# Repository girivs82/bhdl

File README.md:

# BHDL - Board Hardware Description Language

**A modern hardware description language for electronic circuit design with natural flow-based syntax, intelligent analysis, and professional tooling.**

---

## 🎯 Overview

BHDL enables hardware designers to express circuit designs the way they think about them - as **flows of power and signals** between components. With automatic component inference, electrical validation, and comprehensive IDE integration, BHDL brings software-grade tooling to hardware design.

```bhdl
board PowerSupply {
    power VIN = 12V @ 2A;
    ground GND;

    // Flow-based syntax: intuitive and readable
    net regulated: VIN -> reg: LM7805().IN;
    reg.OUT -> @VCC;
    reg.GND -> @GND;

    // Design intent capture
    net filtered: @VCC -> cap: Cap(10µF).1 -> cap.2 -> @GND
        for noise_filtering(cutoff: 100Hz, attenuation: 40dB);
}
```

## ✨ Key Features

### 🌊 Natural Flow-Based Syntax
- **Express circuits as flows**: `VCC -> Res(1kΩ).1 -> LED(red).A -> GND`
- **Component instantiation in-line**: No separate declaration/instantiation
- **Multiple connection operators**: `->` (unidirectional), `<->` (bidirectional), `|>` (flow)
- **Net assignments**: `protected_vin: TVSDiode(15V).K` creates nets with implicit handles

### 🎨 Design Intent System
- **Capture design purpose**: 38 standard intent functions
- **Flow-based annotation**: `for current_limiting(max_current: 20mA)`
- **Automatic synthesis hints**: Tools understand design intent
- **Simulation mode determination**: PureDigital, DigitalWithTiming, MixedSignal, AnalogRequired
- **Validation rules**: Intent-specific checks and recommendations

### 🔬 Advanced Electrical Analysis
- **DC Operating Point**: Newton-Raphson nonlinear solver with component models
- **Safety Analysis**: Automatic derating, current limiting, protection recommendations
- **Component Role Detection**: Topology-based identification without naming conventions
- **Thermal Analysis**: Component temperature and hotspot detection
- **Power Domain Tracking**: Voltage propagation through complex hierarchies

### 📐 Power Domain Scalability
- **Wildcard expansion**: `sensor[*].VCC` → expands to all sensor instances
- **Range expansion**: `fpga.VCCO[0..7]` → 8 indexed pins
- **Automatic decoupling**: Capacitor generation with placement constraints
- **10-100x verbosity reduction** for large designs

### 💻 Professional Tooling

#### Command-Line Interface (CLI)
9 comprehensive commands for the complete workflow:
- `parse` - Syntax validation and AST inspection
- `analyze` - Full 11-pass semantic analysis
- `synthesize` - Netlist generation (JSON/SPICE formats)
- `visualize` - SVG schematic generation
- `spice` - Component role detection and analysis
- `pipeline` - End-to-end workflow automation
- `simulate` - Testbench-driven simulation
- `intents` - Flow tracking and intent analysis
- `doc` - Automatic documentation generation

```bash
# Complete workflow in one command
$ bhdl-cli circuit.bhdl pipeline -o ./build

# Analyze design intents
$ bhdl-cli circuit.bhdl intents

# Generate power domain docs
$ bhdl-cli circuit.bhdl doc -o power_analysis.md
```

#### Language Server Protocol (LSP)
22 major features for IDE integration:
- Real-time diagnostics (parse + semantic)
- Intelligent autocomplete (38 intent functions)
- Hover documentation
- Go to definition / Find references
- Symbol rename with conflict detection
- Document outline and workspace symbols
- Semantic syntax highlighting
- Code actions (quick fixes)
- Inlay hints (type/value display)
- Document formatting
- And 12 more features...

**Works with**: VSCode, Neovim, Emacs, Sublime Text, IntelliJ, and any LSP-compatible editor.

## 🚀 Quick Start

### Prerequisites
- Rust 1.70 or later
- 100MB disk space

### Installation

```bash
# Clone the repository
git clone https://github.com/[USERNAME]/bhdl.git
cd bhdl

# Build all components
cargo build --release

# Run tests
cargo test

# Build CLI
cargo build --release -p bhdl-cli

# Build LSP server
cargo build --release -p bhdl-lsp
```

### Your First Circuit

Create `led_blinker.bhdl`:

```bhdl
entity LED(color: string) {
    pin A: signal in;
    pin K: signal in;
}

entity Resistor(value: resistance) {
    pin 1: signal inout;
    pin 2: signal inout;
}

board LEDBlinker {
    power VCC = 5V @ 100mA;
    ground GND;

    // Current-limited LED with design intent
    net power_to_res: @VCC -> r1: Resistor(330).1;
    net res_to_led: r1.2 -> led1: LED("red").A
        for current_limiting(max_current: 20mA);
    net led_to_gnd: led1.K -> @GND;
}
```

Validate and analyze:

```bash
# Parse the circuit
$ bhdl-cli led_blinker.bhdl parse
✓ Parse successful

# Run analysis
$ bhdl-cli led_blinker.bhdl analyze
✓ Analysis successful - no issues found

# Generate visualization
$ bhdl-cli led_blinker.bhdl visualize -o led_blinker.svg
✓ Visualization generated
```

## 📚 Documentation

| Document | Description |
|----------|-------------|
| [Language Specification](docs/spec/BHDL_Complete_Specification.md) | Complete v2.0 language reference |
| [CLI Guide](docs/implementation/CLI_IMPLEMENTATION_GUIDE.md) | Command-line interface reference |
| [LSP Guide](docs/implementation/LSP_IMPLEMENTATION_SUMMARY.md) | IDE integration guide |
| [Developer Guide](CLAUDE.md) | Architecture and development instructions |
| [Examples](docs/examples/) | Sample circuits and tutorials |
| [Testing Guide](tests/TESTING.md) | Test organization and execution |

## 🏗️ Architecture

The BHDL toolchain follows a multi-stage pipeline:

```
┌──────────────┐    ┌─────────┐    ┌───────────┐    ┌──────────────┐    ┌─────────────┐
│ BHDL Source  │───▶│ Parser  │───▶│ Analyzer  │───▶│ Synthesizer  │───▶│ Visualizer  │
│  (.bhdl)     │    │ (CST)   │    │ (11-pass) │    │  (Netlist)   │    │    (SVG)    │
└──────────────┘    └─────────┘    └───────────┘    └──────────────┘    └─────────────┘
                                           │
                                           ▼
                                    ┌─────────────┐
                                    │ SPICE       │
                                    │ Analysis    │
                                    └─────────────┘
```

### Core Components

#### 1. **bhdl-parser** - Syntax Analysis
- Full v2.0 flow-based syntax support
- Rowan-based incremental parsing
- Comprehensive error recovery
- Electrical unit handling (kΩ, μF, MHz, etc.)

#### 2. **bhdl-analyzer** - Semantic Analysis
11-pass analysis pipeline:
1. **Scope Building**: Symbol tables and definition scopes
2. **Component Registry**: Early instance registration for scalability
3. **Power Domain Expansion**: Wildcards, ranges, and decoupling generation
4. **Reference Resolution**: Type checking and symbol binding
5. **Constant Evaluation**: Compile-time computation
6. **Bounds Checking**: Range validation
7. **Power Analysis**: Voltage propagation and domain tracking
8. **Component Inference**: Automatic component selection
9. **SPICE Synthesis**: Circuit model generation
10. **Attribute Analysis**: Custom attribute handling
11. **Flow Tracking**: Intent resolution and simulation mode determination

#### 3. **bhdl-synthesizer** - Netlist Generation
- Structural netlist output
- Component database integration
- Reference designator auto-generation (R1, D1, C1, etc.)
- Multiple output formats (JSON, SPICE)

#### 4. **bhdl-visualizer** - Schematic Generation
- Semantic layout algorithms
- Force-directed and analytical placement
- Intelligent routing with pathfinding
- Component symbol libraries
- SVG output with embedded metadata

#### 5. **bhdl-spice** - Electrical Analysis
- Newton-Raphson DC solver
- Nonlinear component models
- LED forward voltage modeling
- Diode Shockley equations
- Safety analysis with derating factors

#### 6. **bhdl-stdlib** - Component Library
- Standard component definitions
- Manufacturer datasheet parameters
- Intent function implementations (38 standard intents)
- Behavioral models

#### 7. **bhdl-testbench** - Simulation
- Testbench compiler
- Waveform generation (VCD, CSV, JSON)
- Assertion checking
- Measurement extraction

#### 8. **bhdl-cli** - Command-Line Interface
Production-ready CLI with 9 commands for complete workflow automation.

#### 9. **bhdl-lsp** - Language Server
Production-ready LSP server with 22 features for professional IDE integration.

## 🎓 Language Features

### Flow-Based Connections
```bhdl
// Direct flow syntax
VCC -> Res(1kΩ).1 -> LED(red).A -> GND

// Named nets
net signal_line: sensor.OUT -> filter.IN;

// Bidirectional
data_bus: controller <-> memory;

// With component instantiation
VCC -> r1: Resistor(330).1 -> r1.2 -> led: LED("red").A;
```

### Design Intents
```bhdl
// Capture design purpose
net debounced: button -> rc_filter
    for debounce(time: 50ms);

// Protection intent
net protected: input -> tvs: TVSDiode(6V).K
    for input_protection(max_voltage: 6V);

// Measurement intent
net monitored: @VCC -> sense_resistor -> load
    for current_sensing(max_current: 1A, accuracy: 1%);
```

### Power Domain Scalability
```bhdl
board SensorArray {
    power VCC = 3.3V @ 500mA;

    // Wildcard expansion - connects ALL sensor instances
    power_domain @VCC = 3.3V @ 500mA {
        distribution {
            sensor[*].VCC;  // Expands to sensor_0.VCC, sensor_1.VCC, ...
        }

        decoupling {
            // One capacitor near each sensor
            near sensor[*]: 100nF @ 1;
        }
    }

    // Range expansion - 8 indexed pins
    power_domain @VCCO = 2.5V @ 1A {
        distribution {
            fpga.VCCO[0..7];  // Expands to VCCO0..VCCO7
        }
    }
}
```

### Entity Definitions
```bhdl
entity VoltageRegulator(
    input_voltage: voltage,
    output_voltage: voltage,
    max_current: current
) {
    pin VIN: power in;
    pin VOUT: power out;
    pin GND: ground;
    pin EN: signal in when has_enable_pin;

    // Behavioral specification (optional)
    behavior {
        VOUT = output_voltage;
        efficiency = 0.85;
    }
}
```

### Conditional Logic
```bhdl
// Ternary operator
net regulated: vin -> (use_ldo ? ldo.IN : switcher.IN);

// Conditional pins
pin EN: signal in when has_enable_control;

// Conditional connections
if debug_mode {
    test_points: signals[*] -> TestPoint();
}
```

## 🔧 Development

### Building from Source

```bash
# Debug build (faster compilation)
cargo build

# Release build (optimized)
cargo build --release

# Build specific component
cargo build -p bhdl-analyzer
```

### Running Tests

```bash
# All tests
cargo test

# Specific crate
cargo test -p bhdl-analyzer

# With output
cargo test -- --nocapture

# Single test
cargo test test_name
```

### Code Quality

```bash
# Linting
cargo clippy

# Formatting
cargo fmt

# Check without building
cargo check
```

## 📊 Project Status

| Component | Status | Features | Tests | LOC |
|-----------|--------|----------|-------|-----|
| **Parser** | ✅ Production | Full v2.0 syntax | 150+ | 8,500 |
| **Analyzer** | ✅ Production | 11-pass analysis | 200+ | 15,000 |
| **Synthesizer** | ✅ Production | Multi-format output | 80+ | 5,000 |
| **Visualizer** | ✅ Production | Multiple layouts | 50+ | 6,000 |
| **SPICE** | ✅ Production | DC + safety | 100+ | 8,000 |
| **Stdlib** | ✅ Production | 38 intents | N/A | 3,000 |
| **Testbench** | ✅ Production | Full simulation | 40+ | 4,000 |
| **CLI** | ✅ Production | 9 commands | Validated | 1,050 |
| **LSP** | ✅ Production | 22 features | 92 | 6,117 |
| **Total** | - | - | **700+** | **56,667** |

### Recent Milestones (October 2025)

- ✅ **CLI Implementation**: Complete command-line interface with 9 commands
- ✅ **LSP Server**: Full IDE integration with 22 LSP features
- ✅ **Intent System**: Flow tracking and 38 standard intent functions
- ✅ **Power Domain Expansion**: Wildcards and ranges for scalability
- ✅ **Documentation Generation**: Automatic power domain docs
- ✅ **Unified Simulation**: DC + safety + thermal analysis

### Current Focus

- 🎯 Visualization refinements (symbol scaling, routing optimization)
- 🎯 Additional manufacturer datasheet integration
- 🎯 Community building and example collection
- 🎯 Performance optimization for large designs

## 🤝 Contributing

We welcome contributions! Areas where we'd love help:

- **Component Library**: Add more standard components and models
- **Examples**: Create example circuits and tutorials
- **Documentation**: Improve guides and references
- **Testing**: Add test cases and edge case coverage
- **IDE Extensions**: VSCode, Neovim, Emacs extensions
- **Visualization**: Improve layout algorithms and symbol libraries

See `CONTRIBUTING.md` (TODO) for guidelines.

## 📖 Learning Resources

### Examples

- [Simple LED Circuit](docs/examples/01_simple_led_board.bhdl) - Beginner introduction
- [Multi-LED with Wildcards](docs/examples/02_multi_led_wildcards.bhdl) - Scalability features
- [Sensor Array](docs/examples/03_sensor_array.bhdl) - Ranges and patterns
- [FPGA Dev Board](docs/examples/04_fpga_dev_board.bhdl) - Complex multi-domain design
- [Buck Converter](docs/examples/buck_converter_with_metadata.bhdl) - Advanced features
- [Power Domain Demo](docs/examples/comprehensive_power_demo.bhdl) - All power features

### Tutorials

- [Getting Started](docs/tutorials/getting_started.md) - TODO
- [Design Intents](docs/tutorials/design_intents.md) - TODO
- [Power Domains](docs/tutorials/power_domains.md) - TODO
- [Simulation](docs/tutorials/simulation.md) - TODO

## 🔗 Related Projects

- **KiCad**: PCB design suite (component import)
- **SPICE**: Circuit simulation (netlist export)
- **Verilator**: HDL simulator (digital co-simulation, planned)
- **ngspice**: Open-source SPICE simulator

## 📄 License

Licensed under either of:

- Apache License, Version 2.0 ([LICENSE-APACHE](LICENSE-APACHE) or http://www.apache.org/licenses/LICENSE-2.0)
- MIT license ([LICENSE-MIT](LICENSE-MIT) or http://opensource.org/licenses/MIT)

at your option.

## 🙏 Acknowledgments

BHDL builds on excellent open-source projects:

- **Rowan**: Rust implementation of Red-Green trees for incremental parsing
- **Tower-LSP**: Language Server Protocol framework for Rust
- **Clap**: Command-line argument parsing
- **Serde**: Serialization framework

## 📧 Contact

- **Issues**: [GitHub Issues](https://github.com/[USERNAME]/bhdl/issues)
- **Discussions**: [GitHub Discussions](https://github.com/[USERNAME]/bhdl/discussions)
- **Documentation**: [docs/](docs/)

---

**BHDL** - Hardware description language for the modern age.

*Express circuits naturally. Validate electrically. Design confidently.*

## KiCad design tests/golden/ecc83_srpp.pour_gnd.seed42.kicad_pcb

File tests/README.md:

# BHDL Test Organization

This directory contains all test files and outputs for the BHDL project.

## Directory Structure

```
tests/
├── integration/        # Integration test binaries (.rs files)
│   └── *.rs           # Test binaries that should be in crate src/bin/
├── circuits/          # Test circuit files (.bhdl)
│   ├── simple/        # Simple test circuits
│   ├── realistic/     # Realistic circuits (7805, etc.)
│   └── edge_cases/    # Edge case testing
├── outputs/           # Test outputs (SVG, logs, etc.)
│   ├── svg/           # Generated circuit visualizations
│   └── netlists/      # Generated netlist outputs
└── scratch/           # Temporary test files (git-ignored)
```

## Running Tests

### Unit Tests
```bash
# Run all unit tests
cargo test

# Run tests for specific crate
cargo test -p bhdl-analyzer
cargo test -p bhdl-synthesizer
```

### Integration Tests
Integration test binaries should be placed in the appropriate crate's `src/bin/` directory:
- `bhdl-analyzer/src/bin/` - Analyzer test binaries
- `bhdl-synthesizer/src/bin/` - Synthesizer test binaries
- `bhdl-visualizer/src/bin/` - Visualizer test binaries

Run them with:
```bash
cargo run -p <crate-name> --bin <test-name>
```

### Test Circuits
Test circuits should be organized in `tests/circuits/`:
- Use descriptive names
- Group by complexity or feature being tested
- Document what each circuit tests

## Guidelines

1. **No test files in project root** - All test files belong here
2. **Clean up after tests** - Don't leave temporary files around
3. **Use scratch/ for experiments** - This directory is git-ignored
4. **Organize by purpose** - Keep similar tests together
5. **Document test purpose** - Each test should explain what it's testing

## Migration TODO
- [ ] Move all *.rs test files from root to appropriate crate bins
- [ ] Move all test *.bhdl files to tests/circuits/
- [ ] Move all *.svg outputs to tests/outputs/svg/
- [ ] Update test runners to use new paths
- [ ] Add tests/scratch/ to .gitignore

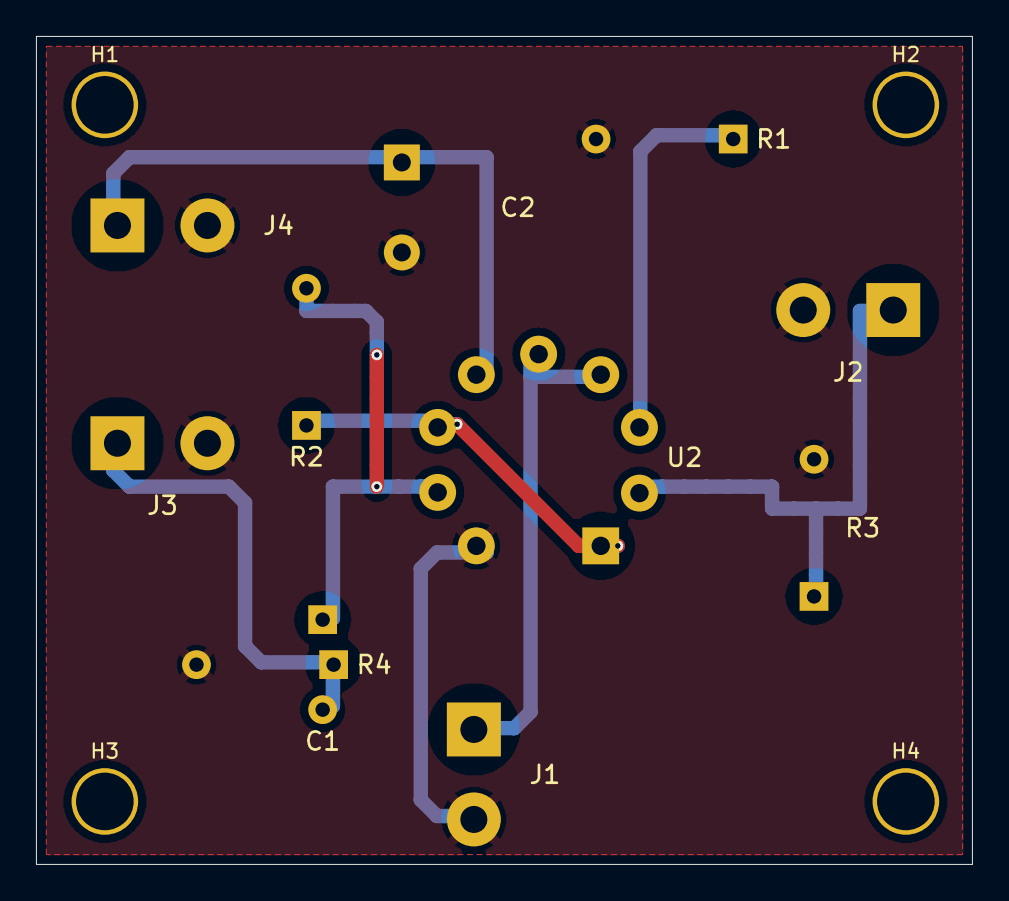
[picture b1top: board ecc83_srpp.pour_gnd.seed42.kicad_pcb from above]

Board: 2 copper layers, 52.0 x 46.0 mm, 15 parts (0 on the bottom side), 8 nets.

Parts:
C1: c_out; Disc-P5.00
C2: c_res; Radial-P5.00-D10
H1, H2, H3, H4: MountingHole_3.2mm
J1: J_HTR; TerminalBlock-P5.00-1x02
J2: J_IN; TerminalBlock-P5.00-1x02
J3: J_OUT; TerminalBlock-P5.00-1x02
J4: J_PWR; TerminalBlock-P5.00-1x02
R1: r_klo; Axial-P7.62
R2: r_kup; Axial-P7.62
R3: r_leak; Axial-P7.62
R4: r_load; Axial-P7.62
U2: u1_V; Valve-Noval

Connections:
GND: C2.neg, J1.2, J2.2, J3.2, J4.2, R1.2, R3.2, R4.2, U2.9
HTR: J1.1, U2.4, U2.5
VBB: C2.pos, J4.1, U2.6
auto_J_IN_1: J2.1, R3.1, U2.2
auto_c_out_2: C1.2, J3.1, R4.1
auto_r_kup_2: C1.1, R2.2, U2.8
auto_u1_A1: R2.1, U2.1, U2.7
auto_u1_K1: R1.1, U2.3

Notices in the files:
README.md:
License: MIT OR Apache-2.0
